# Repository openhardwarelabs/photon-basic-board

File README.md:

# photon-basic-board
Basic sensor board based on the Particle Photon PCB mount board

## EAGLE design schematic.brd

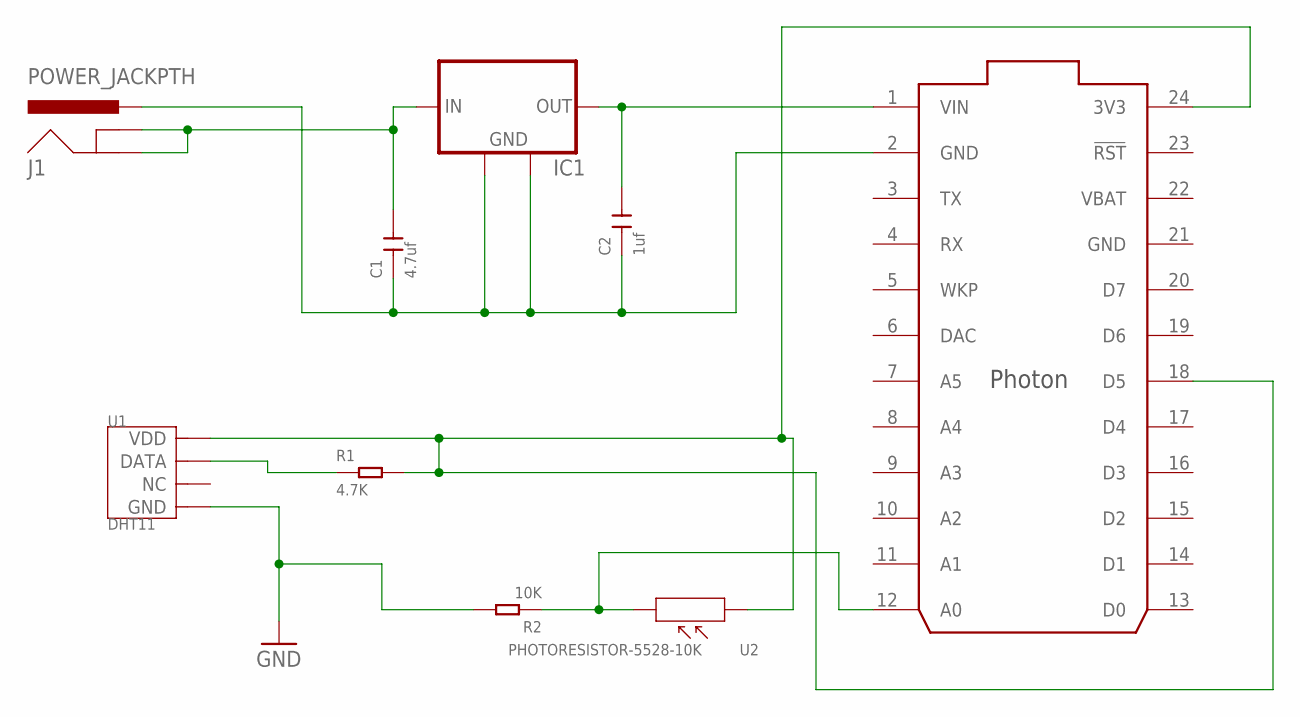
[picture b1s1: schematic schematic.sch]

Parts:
C1: 4.7uf; C1206
C2: 1uf; C0805
IC1: MCP1825S-SOT223; SOT223
J1: POWER_JACKPTH; POWER_JACK_PTH
R1: 4.7K; PR-D2.3XL6.5MM
R2: 10K; PR-D2.3XL6.5MM
U1: DHT11; SNR4-2.54-15.5X12.0X5.5MM
U2: PHOTORESISTOR-5528-10K; SNR2-3.0
U$1: PHOTON_SMD

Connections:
GND: R2.2, U1.4 (GND), U$1.21 (GND)
unnamed: C1.1, C2.1, IC1.2 (GND), IC1.4 (GND), J1.PWR, U$1.2 (GND)
unnamed: R1.1, U1.2 (DATA)
unnamed: C1.2, IC1.1 (IN), J1.GND, J1.GNDBREAK
unnamed: C2.2, IC1.3 (OUT), U$1.1 (VIN)
unnamed: R2.1, U2.2, U$1.12 (A0)
VBAT: U$1.22 (VBAT)
VDD: R1.2, U1.1 (VDD), U2.1, U$1.18 (D5), U$1.24 (3V3)

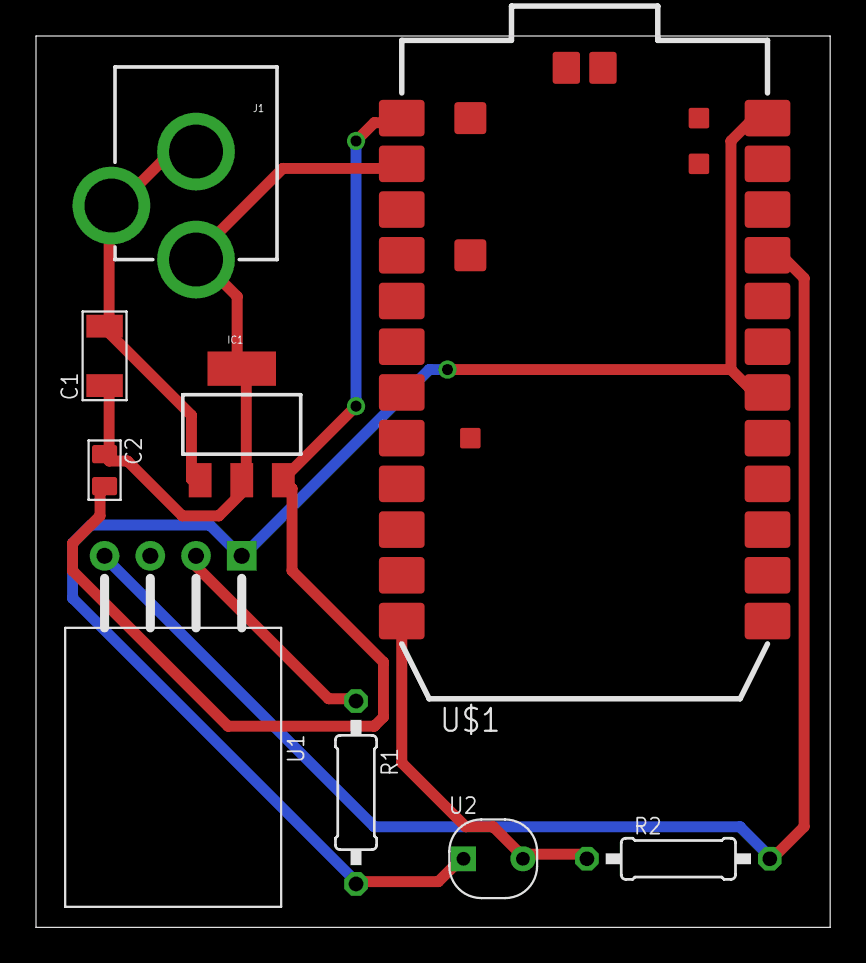
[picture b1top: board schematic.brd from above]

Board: 2 copper layers, 44.1 x 49.5 mm, 9 parts (0 on the bottom side), 7 nets.

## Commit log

2015-09-07 added files
